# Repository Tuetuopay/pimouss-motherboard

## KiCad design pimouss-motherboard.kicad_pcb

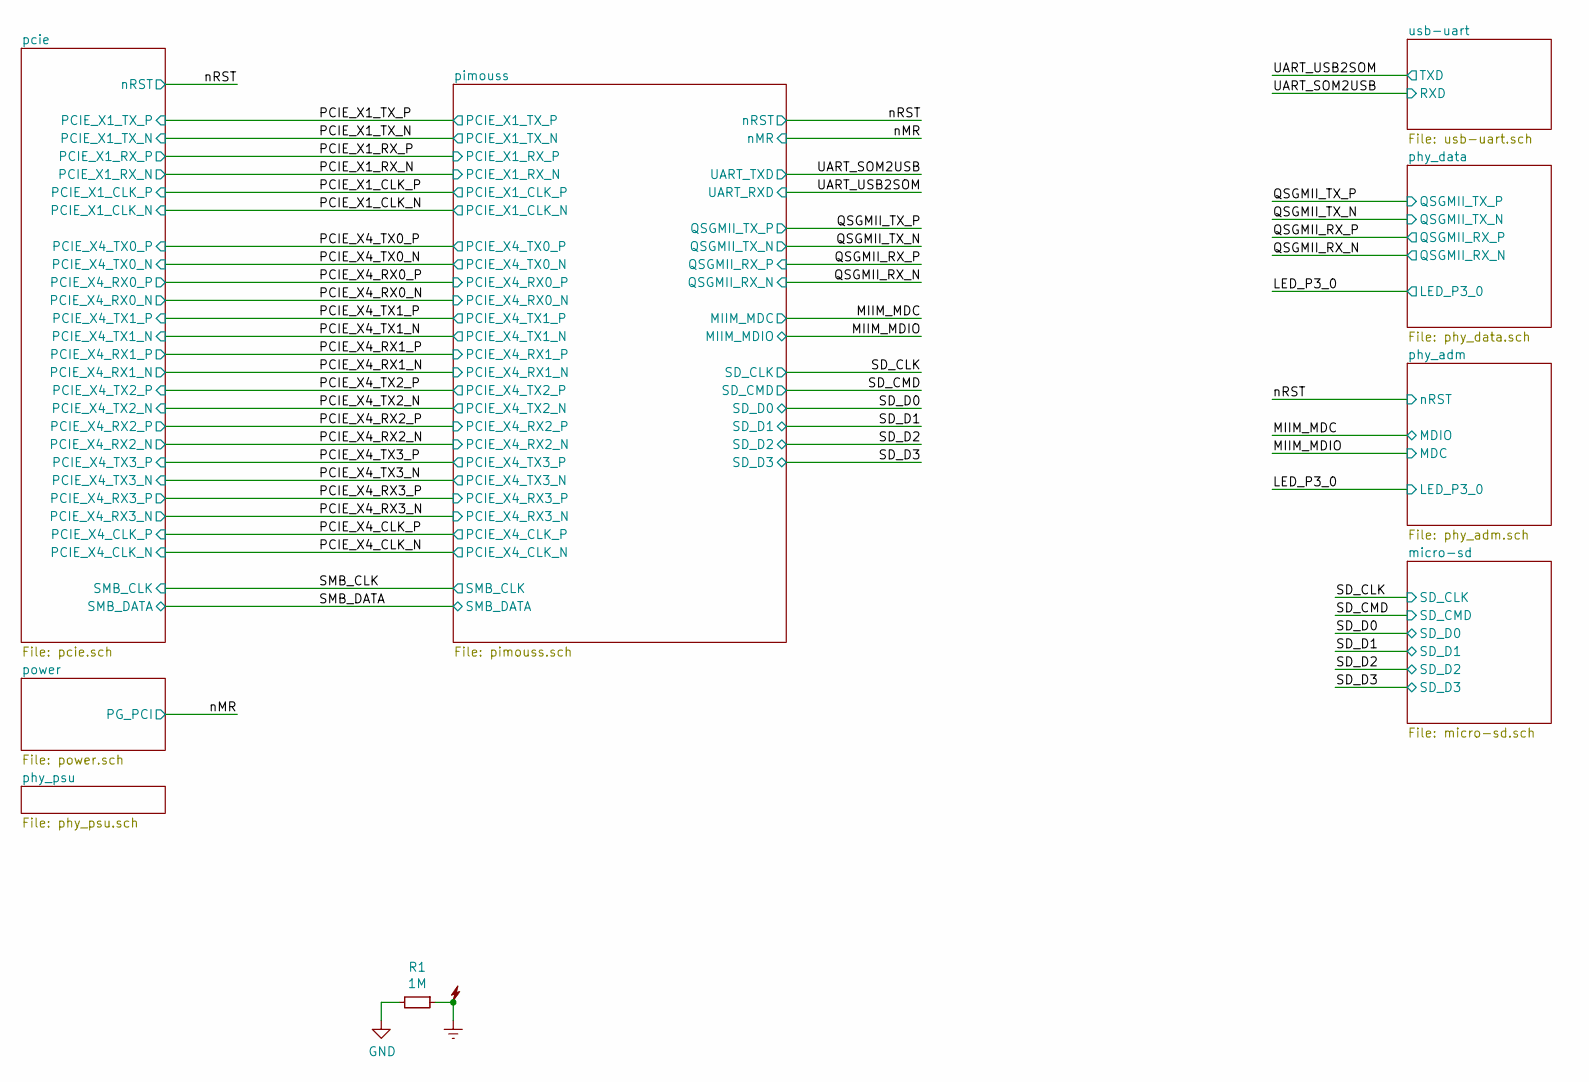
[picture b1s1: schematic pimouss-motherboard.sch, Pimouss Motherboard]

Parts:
R1: 1M; R_0603_1608Metric

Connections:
Earth: R1.1; also elsewhere on the board

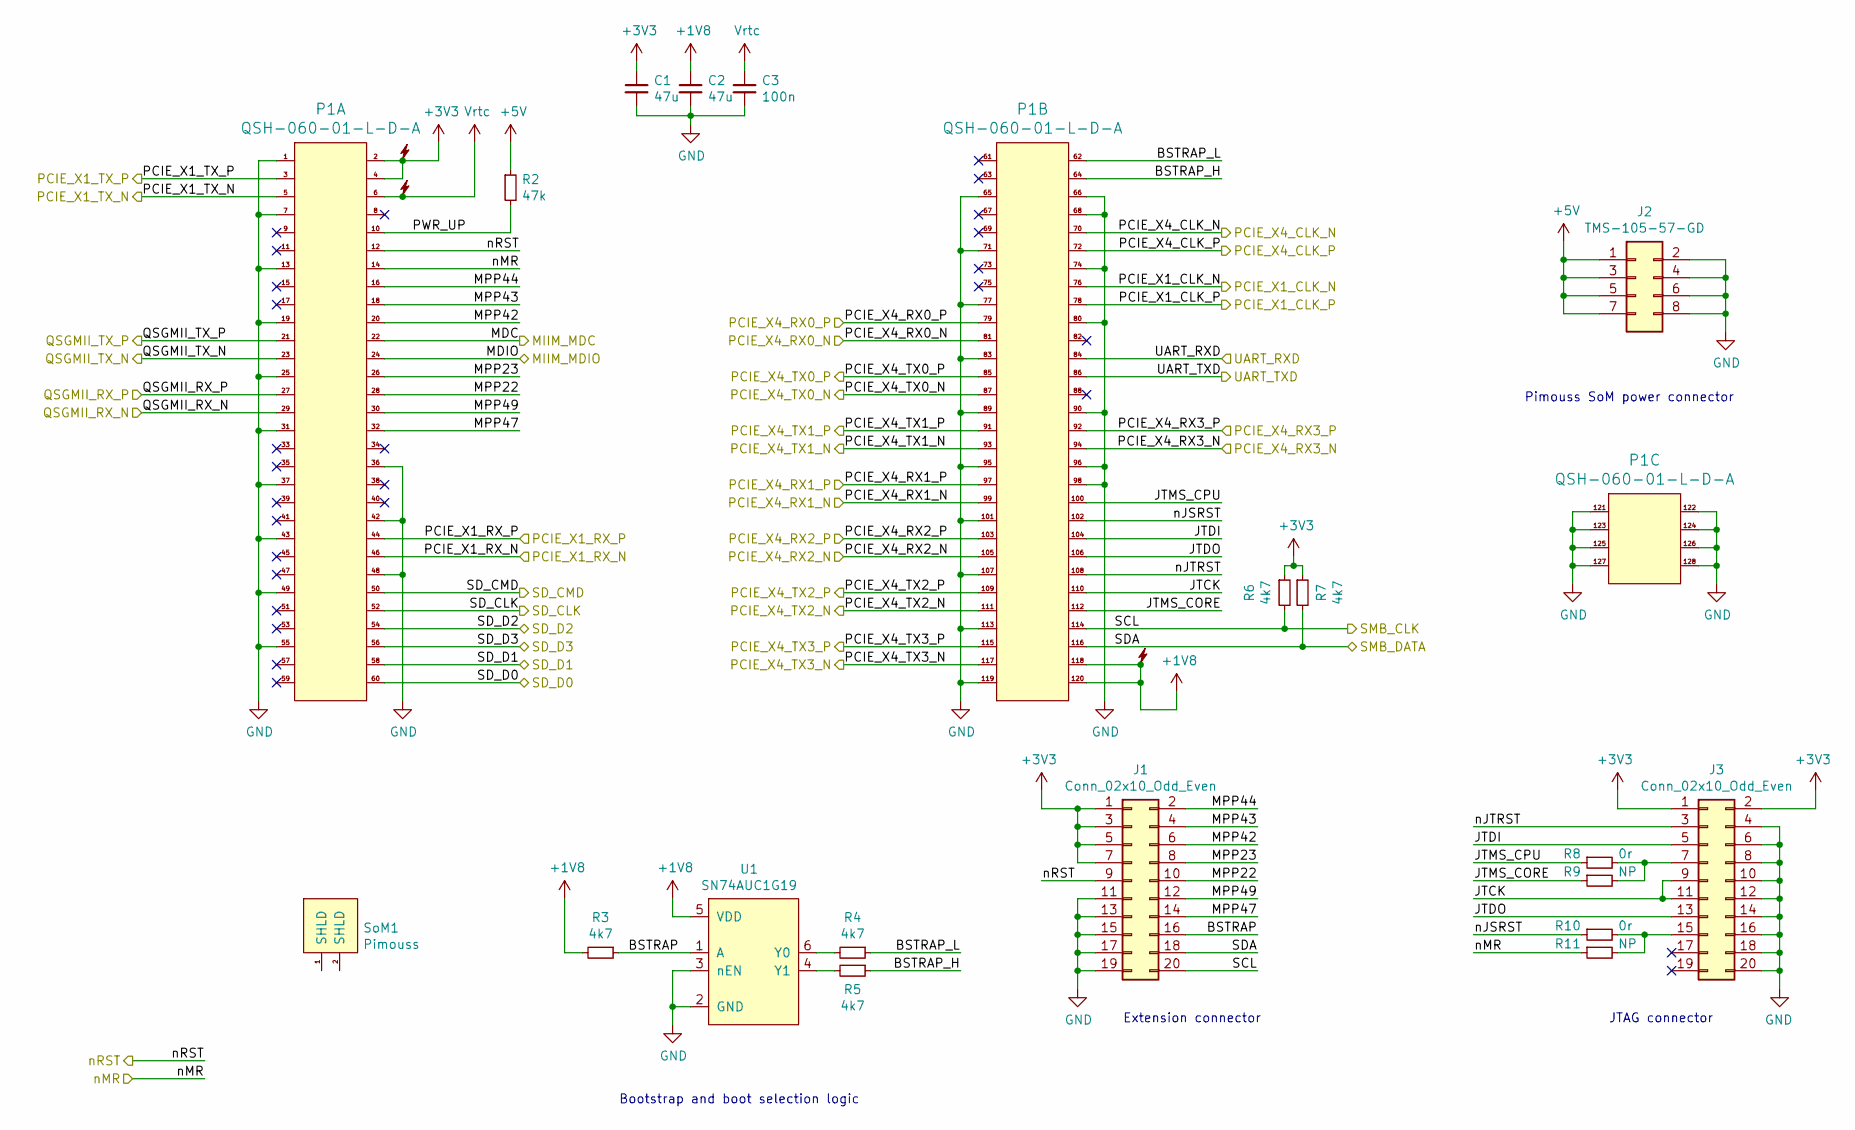
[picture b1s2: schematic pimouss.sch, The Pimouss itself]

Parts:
C1, C2: 47u; C_0805_2012Metric
C3: 100n; C_0603_1608Metric
J1, J3: Conn_02x10_Odd_Even; PinHeader_2x10_P2.54mm_Vertical
J2: TMS-105-57-GD; TMS-105-57-G-D
P1: QSH-060-01-L-D-A
R2: 47k; R_0603_1608Metric
R3, R4, R5, R6, R7: 4k7; R_0603_1608Metric
R8, R10: 0r; R_0603_1608Metric
R9, R11: NP; R_0603_1608Metric
SoM1: Pimouss
U1: SN74AUC1G19; SOT-23-6

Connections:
/MIIM_MDC: P1.22; also elsewhere on the board
/MIIM_MDIO: P1.24; also elsewhere on the board
/PCIE_X1_CLK_N: P1.76; also elsewhere on the board
/PCIE_X1_CLK_P: P1.78; also elsewhere on the board
/PCIE_X1_RX_N: P1.46; also elsewhere on the board
/PCIE_X1_RX_P: P1.44; also elsewhere on the board
/PCIE_X1_TX_N: P1.5; also elsewhere on the board
/PCIE_X1_TX_P: P1.3; also elsewhere on the board
/PCIE_X4_CLK_N: P1.70; also elsewhere on the board
/PCIE_X4_CLK_P: P1.72; also elsewhere on the board
/PCIE_X4_RX0_N: P1.81; also elsewhere on the board
/PCIE_X4_RX0_P: P1.79; also elsewhere on the board
/PCIE_X4_RX1_N: P1.99; also elsewhere on the board
/PCIE_X4_RX1_P: P1.97; also elsewhere on the board
/PCIE_X4_RX2_N: P1.105; also elsewhere on the board
/PCIE_X4_RX2_P: P1.103; also elsewhere on the board
/PCIE_X4_RX3_N: P1.94; also elsewhere on the board
/PCIE_X4_RX3_P: P1.92; also elsewhere on the board
/PCIE_X4_TX0_N: P1.87; also elsewhere on the board
/PCIE_X4_TX0_P: P1.85; also elsewhere on the board
/PCIE_X4_TX1_N: P1.93; also elsewhere on the board
/PCIE_X4_TX1_P: P1.91; also elsewhere on the board
/PCIE_X4_TX2_N: P1.111; also elsewhere on the board
/PCIE_X4_TX2_P: P1.109; also elsewhere on the board
/PCIE_X4_TX3_N: P1.117; also elsewhere on the board
/PCIE_X4_TX3_P: P1.115; also elsewhere on the board
/QSGMII_RX_N: P1.29; also elsewhere on the board
/QSGMII_RX_P: P1.27; also elsewhere on the board
/QSGMII_TX_N: P1.23; also elsewhere on the board
/QSGMII_TX_P: P1.21; also elsewhere on the board
/SD_CLK: P1.52; also elsewhere on the board
/SD_CMD: P1.50; also elsewhere on the board
/SD_D0: P1.60; also elsewhere on the board
/SD_D1: P1.58; also elsewhere on the board
/SD_D2: P1.54; also elsewhere on the board
/SD_D3: P1.56; also elsewhere on the board
/SMB_CLK: J1.20, P1.114, R6.2; also elsewhere on the board
/SMB_DATA: J1.18, P1.116, R7.2; also elsewhere on the board
/UART_SOM2USB: P1.86; also elsewhere on the board
/UART_USB2SOM: P1.84; also elsewhere on the board
/nMR: P1.14, R11.1; also elsewhere on the board
/nRST: J1.9, P1.12; also elsewhere on the board
/pimouss/BSTRAP: J1.16, R3.1, U1.1 (A)
/pimouss/BSTRAP_H: P1.64, R5.1
/pimouss/BSTRAP_L: P1.62, R4.1
/pimouss/JTCK: J3.9, J3.11, P1.110
/pimouss/JTDI: J3.5, P1.104
/pimouss/JTDO: J3.13, P1.106
/pimouss/JTMS_CORE: P1.112, R9.1
/pimouss/JTMS_CPU: P1.100, R8.1
/pimouss/MPP22: J1.10, P1.28
/pimouss/MPP23: J1.8, P1.26
/pimouss/MPP42: J1.6, P1.20
/pimouss/MPP43: J1.4, P1.18
/pimouss/MPP44: J1.2, P1.16
/pimouss/MPP47: J1.14, P1.32
/pimouss/MPP49: J1.12, P1.30
/pimouss/PWR_UP: P1.10, R2.2
/pimouss/nJSRST: P1.102, R10.1
/pimouss/nJTRST: J3.3, P1.108
unnamed: J3.7, R8.2, R9.2
unnamed: J3.15, R10.2, R11.2
unnamed: R4.2, U1.6 (Y0)
unnamed: R5.2, U1.4 (Y1)

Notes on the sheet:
Pimouss SoM power connector
Bootstrap and boot selection logic
JTAG connector
Extension connector

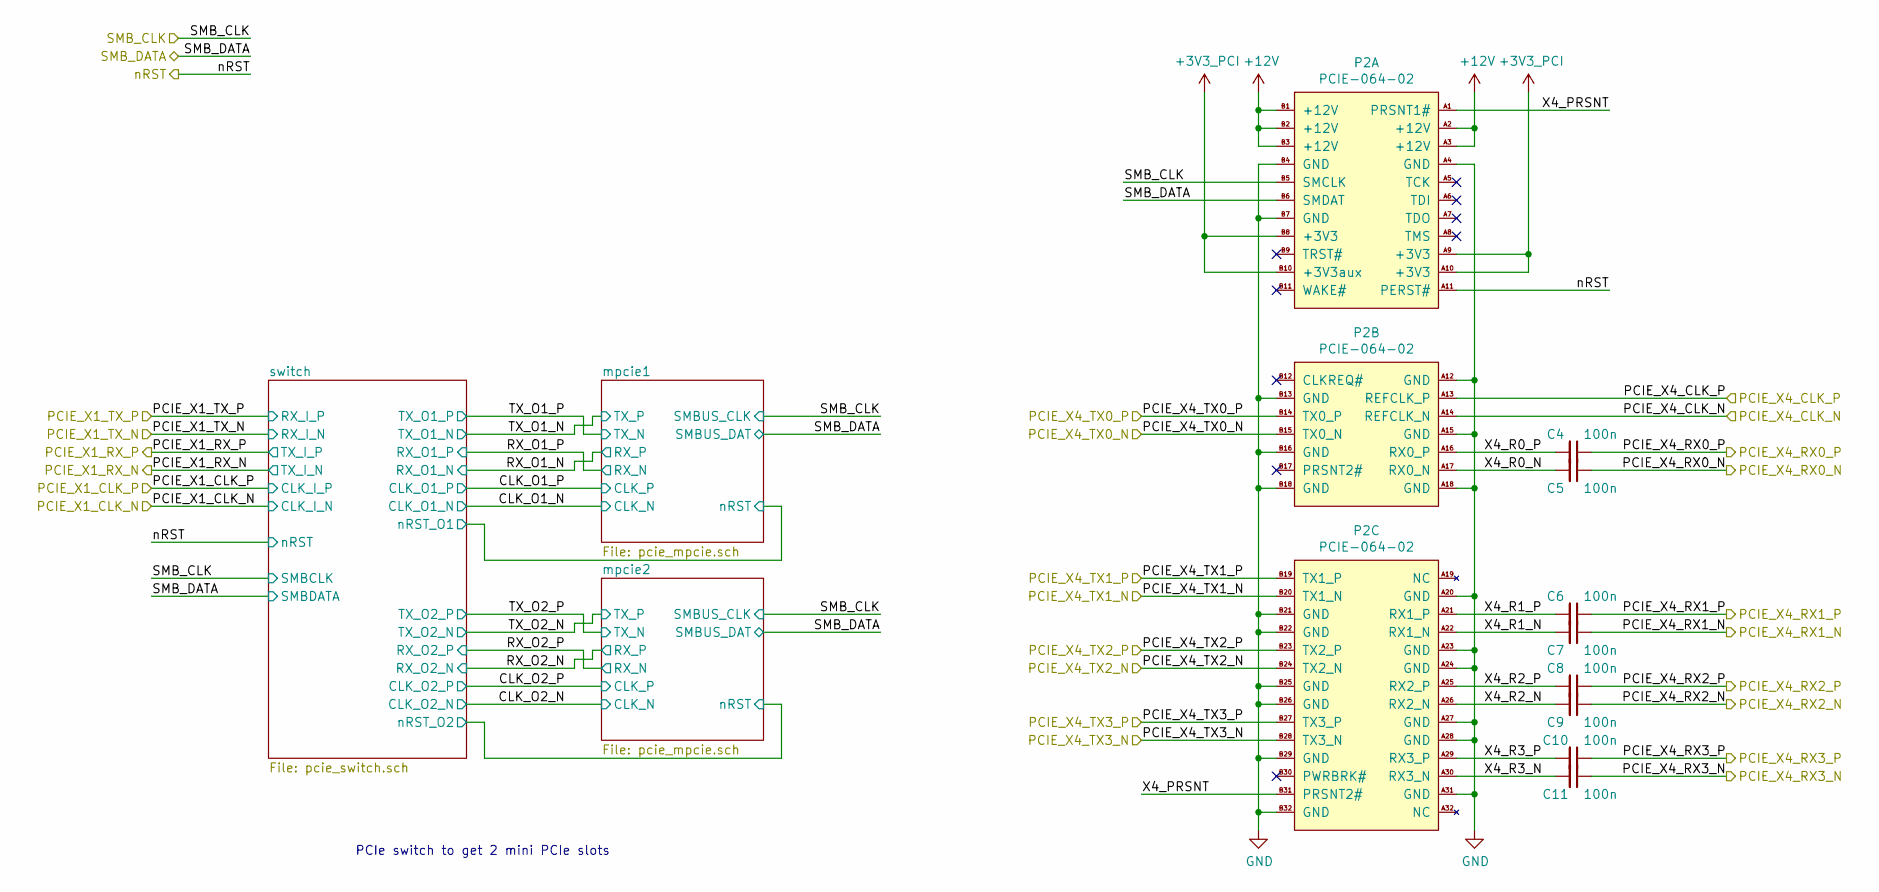
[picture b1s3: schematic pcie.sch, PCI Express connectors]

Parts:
C4, C5, C6, C7, C8, C9, C10, C11: 100n; C_0402_1005Metric
P2: PCIE-064-02; SAMTEC_PCIE-064-02-F-D-TH

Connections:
/PCIE_X4_CLK_N: P2.A14 (REFCLK_N); also elsewhere on the board
/PCIE_X4_CLK_P: P2.A13 (REFCLK_P); also elsewhere on the board
/PCIE_X4_RX0_N: C5.1; also elsewhere on the board
/PCIE_X4_RX0_P: C4.1; also elsewhere on the board
/PCIE_X4_RX1_N: C7.1; also elsewhere on the board
/PCIE_X4_RX1_P: C6.1; also elsewhere on the board
/PCIE_X4_RX2_N: C9.1; also elsewhere on the board
/PCIE_X4_RX2_P: C8.1; also elsewhere on the board
/PCIE_X4_RX3_N: C11.1; also elsewhere on the board
/PCIE_X4_RX3_P: C10.1; also elsewhere on the board
/PCIE_X4_TX0_N: P2.B15 (TX0_N); also elsewhere on the board
/PCIE_X4_TX0_P: P2.B14 (TX0_P); also elsewhere on the board
/PCIE_X4_TX1_N: P2.B20 (TX1_N); also elsewhere on the board
/PCIE_X4_TX1_P: P2.B19 (TX1_P); also elsewhere on the board
/PCIE_X4_TX2_N: P2.B24 (TX2_N); also elsewhere on the board
/PCIE_X4_TX2_P: P2.B23 (TX2_P); also elsewhere on the board
/PCIE_X4_TX3_N: P2.B28 (TX3_N); also elsewhere on the board
/PCIE_X4_TX3_P: P2.B27 (TX3_P); also elsewhere on the board
/SMB_CLK: P2.B5 (SMCLK); also elsewhere on the board
/SMB_DATA: P2.B6 (SMDAT); also elsewhere on the board
/nRST: P2.A11 (PERST#); also elsewhere on the board
/pcie/X4_PRSNT: P2.A1 (PRSNT1#), P2.B31 (PRSNT2#)
/pcie/X4_R0_N: C5.2, P2.A17 (RX0_N)
/pcie/X4_R0_P: C4.2, P2.A16 (RX0_P)
/pcie/X4_R1_N: C7.2, P2.A22 (RX1_N)
/pcie/X4_R1_P: C6.2, P2.A21 (RX1_P)
/pcie/X4_R2_N: C9.2, P2.A26 (RX2_N)
/pcie/X4_R2_P: C8.2, P2.A25 (RX2_P)
/pcie/X4_R3_N: C11.2, P2.A30 (RX3_N)
/pcie/X4_R3_P: C10.2, P2.A29 (RX3_P)

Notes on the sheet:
PCIe switch to get 2 mini PCIe slots

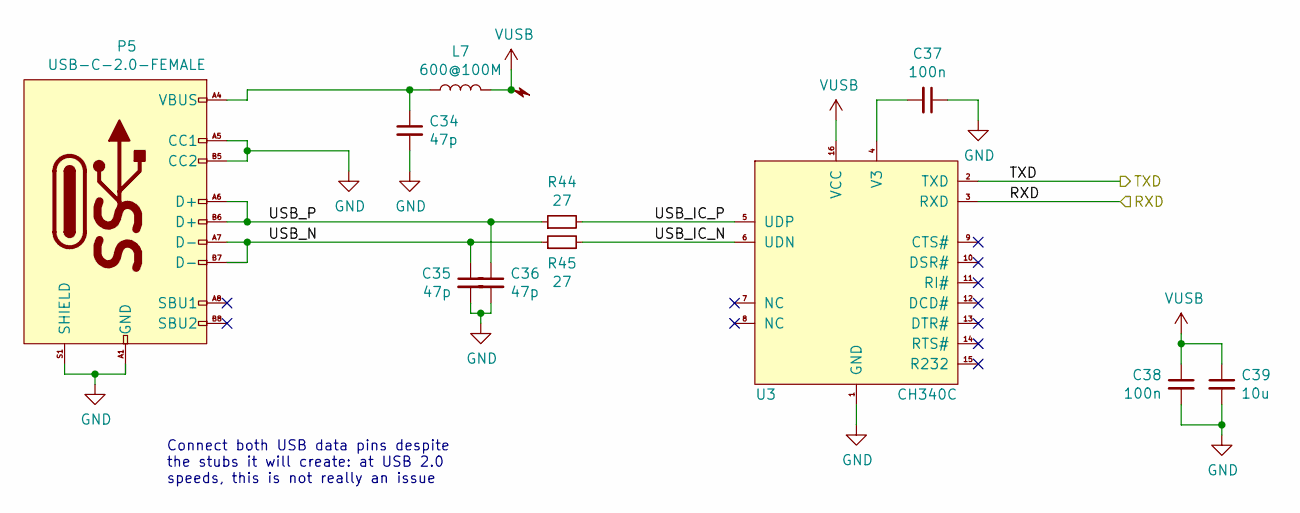
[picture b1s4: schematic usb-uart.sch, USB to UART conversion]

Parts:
C34, C35, C36: 47p; C_0603_1608Metric
C37, C38: 100n; C_0603_1608Metric
C39: 10u; C_0603_1608Metric
L7: 600@100M; L_0603_1608Metric
P5: USB-C-2.0-FEMALE; USB-C-FEMALE
R44, R45: 27; R_0603_1608Metric
U3: CH340C; SSOP-20_5.3x7.2mm_P0.65mm

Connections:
/UART_SOM2USB: U3.3 (RXD); also elsewhere on the board
/UART_USB2SOM: U3.2 (TXD); also elsewhere on the board
/usb-uart/USB_IC_N: R45.2, U3.6 (UDN)
/usb-uart/USB_IC_P: R44.2, U3.5 (UDP)
/usb-uart/USB_N: C35.1, P5.A7 (D-), P5.B7 (D-), R45.1
/usb-uart/USB_P: C36.1, P5.A6 (D+), P5.B6 (D+), R44.1
unnamed: C34.1, L7.1, P5.A4 (VBUS), P5.A9 (VBUS), P5.B4 (VBUS), P5.B9 (VBUS)
unnamed: C37.2, U3.4 (V3)
VUSB: C38.1, C39.1, L7.2, U3.16 (VCC)

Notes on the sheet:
Connect both USB data pins despite the stubs it will create: at USB 2.0 speeds, this is not really an issue

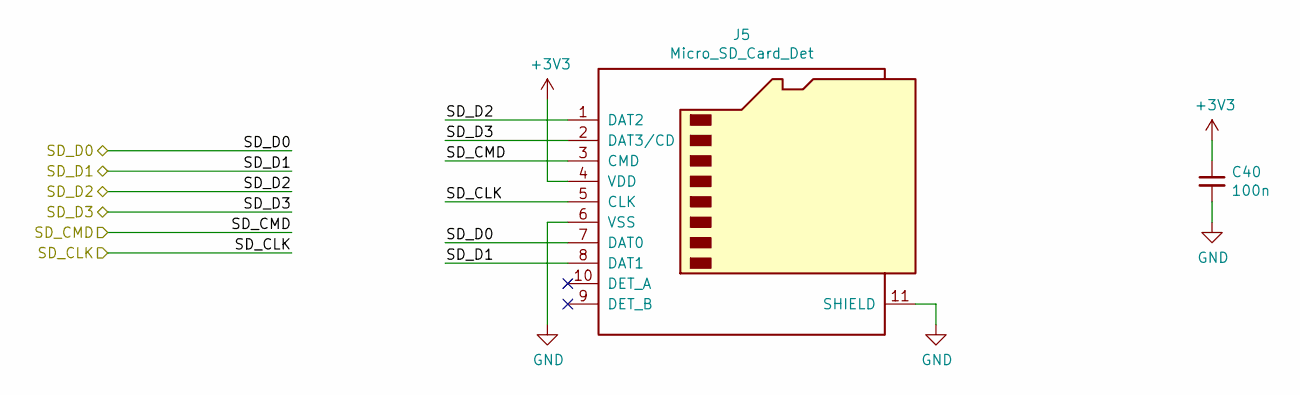
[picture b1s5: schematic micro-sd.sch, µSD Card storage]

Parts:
C40: 100n; C_0603_1608Metric
J5: Micro_SD_Card_Det; microSD_HC_Hirose_DM3D-SF

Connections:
/SD_CLK: J5.5 (CLK); also elsewhere on the board
/SD_CMD: J5.3 (CMD); also elsewhere on the board
/SD_D0: J5.7 (DAT0); also elsewhere on the board
/SD_D1: J5.8 (DAT1); also elsewhere on the board
/SD_D2: J5.1 (DAT2); also elsewhere on the board
/SD_D3: J5.2 (DAT3/CD); also elsewhere on the board

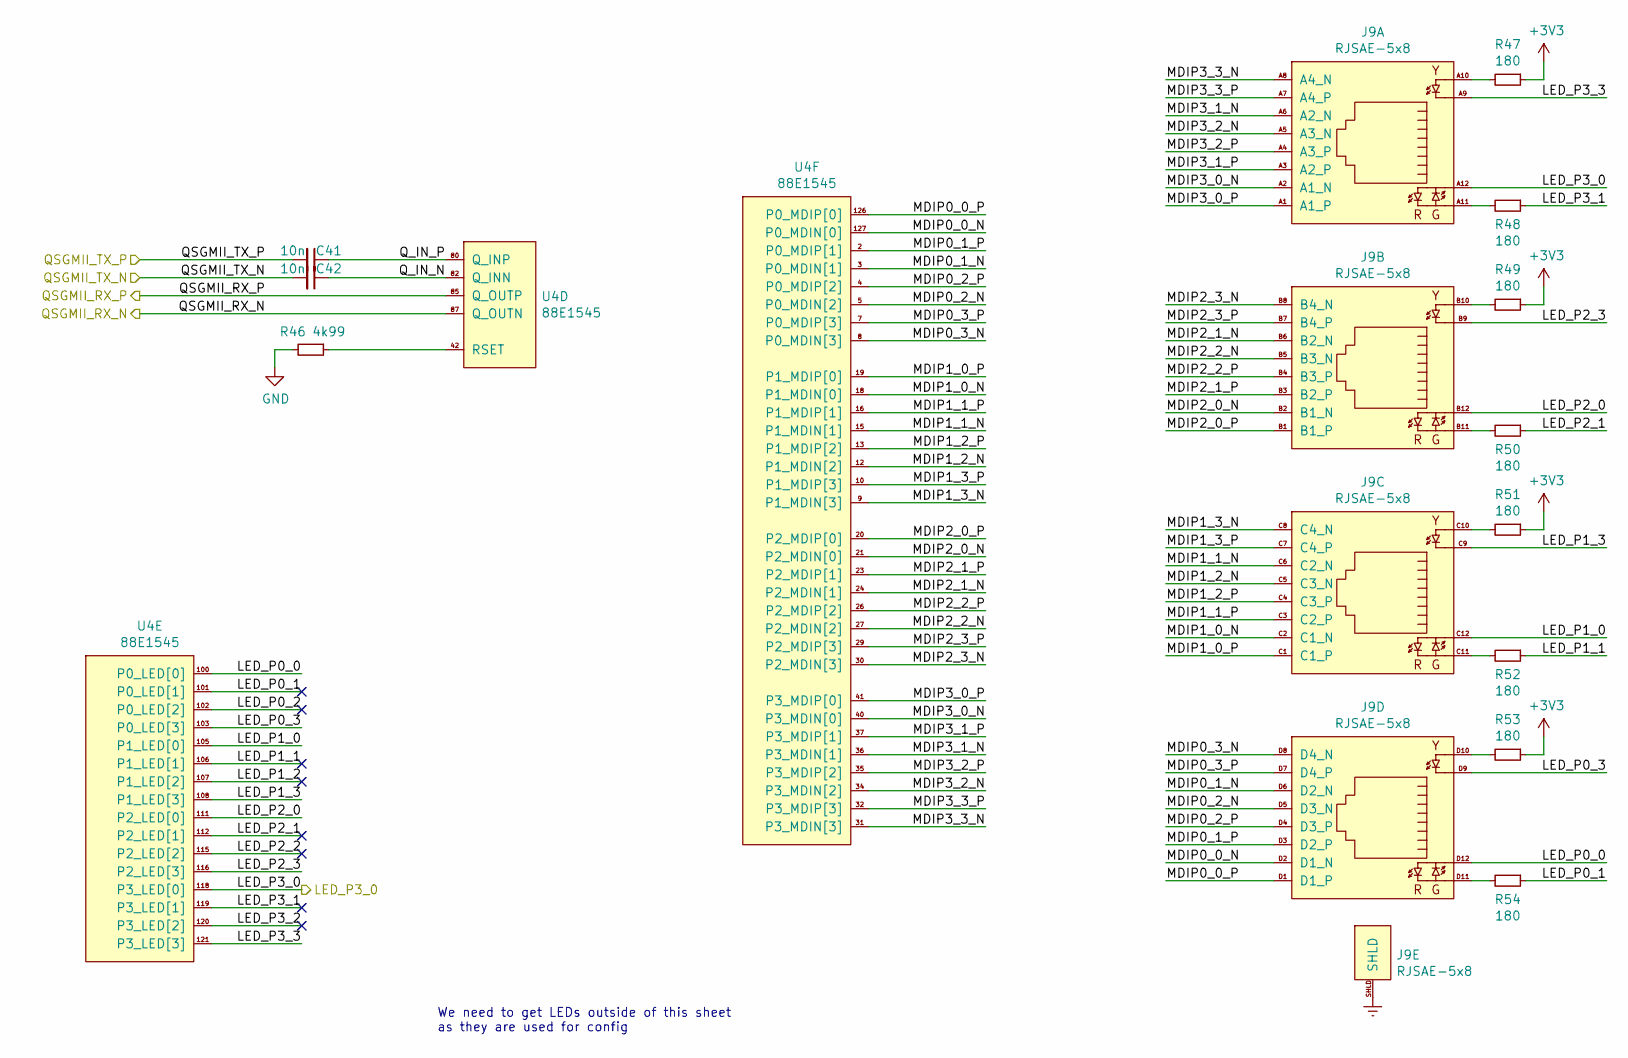
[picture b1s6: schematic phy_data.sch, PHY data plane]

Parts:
C41, C42: 10n; C_0402_1005Metric
J9: RJSAE-5x8
R46: 4k99; R_0603_1608Metric
R47, R48, R49, R50, R51, R52, R53, R54: 180; R_0603_1608Metric
U4: 88E1545; LQFP-128-1EP_14x20mm_P0.5mm_EP3.93x6.42mm

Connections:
/LED_P3_0: J9.A12, U4.118 (P3_LED[0]); also elsewhere on the board
/QSGMII_RX_N: U4.87 (Q_OUTN); also elsewhere on the board
/QSGMII_RX_P: U4.85 (Q_OUTP); also elsewhere on the board
/QSGMII_TX_N: C42.2; also elsewhere on the board
/QSGMII_TX_P: C41.2; also elsewhere on the board
/phy_data/LED_P0_0: J9.D12, U4.100 (P0_LED[0])
/phy_data/LED_P0_1: R54.1, U4.101 (P0_LED[1])
/phy_data/LED_P0_2: U4.102 (P0_LED[2])
/phy_data/LED_P0_3: J9.D9, U4.103 (P0_LED[3])
/phy_data/LED_P1_0: J9.C12, U4.105 (P1_LED[0])
/phy_data/LED_P1_1: R52.1, U4.106 (P1_LED[1])
/phy_data/LED_P1_2: U4.107 (P1_LED[2])
/phy_data/LED_P1_3: J9.C9, U4.108 (P1_LED[3])
/phy_data/LED_P2_0: J9.B12, U4.111 (P2_LED[0])
/phy_data/LED_P2_1: R50.1, U4.112 (P2_LED[1])
/phy_data/LED_P2_2: U4.115 (P2_LED[2])
/phy_data/LED_P2_3: J9.B9, U4.116 (P2_LED[3])
/phy_data/LED_P3_1: R48.1, U4.119 (P3_LED[1])
/phy_data/LED_P3_2: U4.120 (P3_LED[2])
/phy_data/LED_P3_3: J9.A9, U4.121 (P3_LED[3])
/phy_data/MDIP0_0_N: J9.D2 (D1_N), U4.127 (P0_MDIN[0])
/phy_data/MDIP0_0_P: J9.D1 (D1_P), U4.126 (P0_MDIP[0])
/phy_data/MDIP0_1_N: J9.D6 (D2_N), U4.3 (P0_MDIN[1])
/phy_data/MDIP0_1_P: J9.D3 (D2_P), U4.2 (P0_MDIP[1])
/phy_data/MDIP0_2_N: J9.D5 (D3_N), U4.5 (P0_MDIN[2])
/phy_data/MDIP0_2_P: J9.D4 (D3_P), U4.4 (P0_MDIP[2])
/phy_data/MDIP0_3_N: J9.D8 (D4_N), U4.8 (P0_MDIN[3])
/phy_data/MDIP0_3_P: J9.D7 (D4_P), U4.7 (P0_MDIP[3])
/phy_data/MDIP1_0_N: J9.C2 (C1_N), U4.18 (P1_MDIN[0])
/phy_data/MDIP1_0_P: J9.C1 (C1_P), U4.19 (P1_MDIP[0])
/phy_data/MDIP1_1_N: J9.C6 (C2_N), U4.15 (P1_MDIN[1])
/phy_data/MDIP1_1_P: J9.C3 (C2_P), U4.16 (P1_MDIP[1])
/phy_data/MDIP1_2_N: J9.C5 (C3_N), U4.12 (P1_MDIN[2])
/phy_data/MDIP1_2_P: J9.C4 (C3_P), U4.13 (P1_MDIP[2])
/phy_data/MDIP1_3_N: J9.C8 (C4_N), U4.9 (P1_MDIN[3])
/phy_data/MDIP1_3_P: J9.C7 (C4_P), U4.10 (P1_MDIP[3])
/phy_data/MDIP2_0_N: J9.B2 (B1_N), U4.21 (P2_MDIN[0])
/phy_data/MDIP2_0_P: J9.B1 (B1_P), U4.20 (P2_MDIP[0])
/phy_data/MDIP2_1_N: J9.B6 (B2_N), U4.24 (P2_MDIN[1])
/phy_data/MDIP2_1_P: J9.B3 (B2_P), U4.23 (P2_MDIP[1])
/phy_data/MDIP2_2_N: J9.B5 (B3_N), U4.27 (P2_MDIN[2])
/phy_data/MDIP2_2_P: J9.B4 (B3_P), U4.26 (P2_MDIP[2])
/phy_data/MDIP2_3_N: J9.B8 (B4_N), U4.30 (P2_MDIN[3])
/phy_data/MDIP2_3_P: J9.B7 (B4_P), U4.29 (P2_MDIP[3])
/phy_data/MDIP3_0_N: J9.A2 (A1_N), U4.40 (P3_MDIN[0])
/phy_data/MDIP3_0_P: J9.A1 (A1_P), U4.41 (P3_MDIP[0])
/phy_data/MDIP3_1_N: J9.A6 (A2_N), U4.36 (P3_MDIN[1])
/phy_data/MDIP3_1_P: J9.A3 (A2_P), U4.37 (P3_MDIP[1])
/phy_data/MDIP3_2_N: J9.A5 (A3_N), U4.34 (P3_MDIN[2])
/phy_data/MDIP3_2_P: J9.A4 (A3_P), U4.35 (P3_MDIP[2])
/phy_data/MDIP3_3_N: J9.A8 (A4_N), U4.31 (P3_MDIN[3])
/phy_data/MDIP3_3_P: J9.A7 (A4_P), U4.32 (P3_MDIP[3])
/phy_data/Q_IN_N: C42.1, U4.82 (Q_INN)
/phy_data/Q_IN_P: C41.1, U4.80 (Q_INP)
Earth: J9.SHLD; also elsewhere on the board
unnamed: J9.A10, R47.2
unnamed: J9.A11, R48.2
unnamed: J9.B10, R49.2
unnamed: J9.B11, R50.2
unnamed: J9.C10, R51.2
unnamed: J9.C11, R52.2
unnamed: J9.D10, R53.2
unnamed: J9.D11, R54.2
unnamed: R46.1, U4.42 (RSET)

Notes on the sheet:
We need to get LEDs outside of this sheet as they are used for config

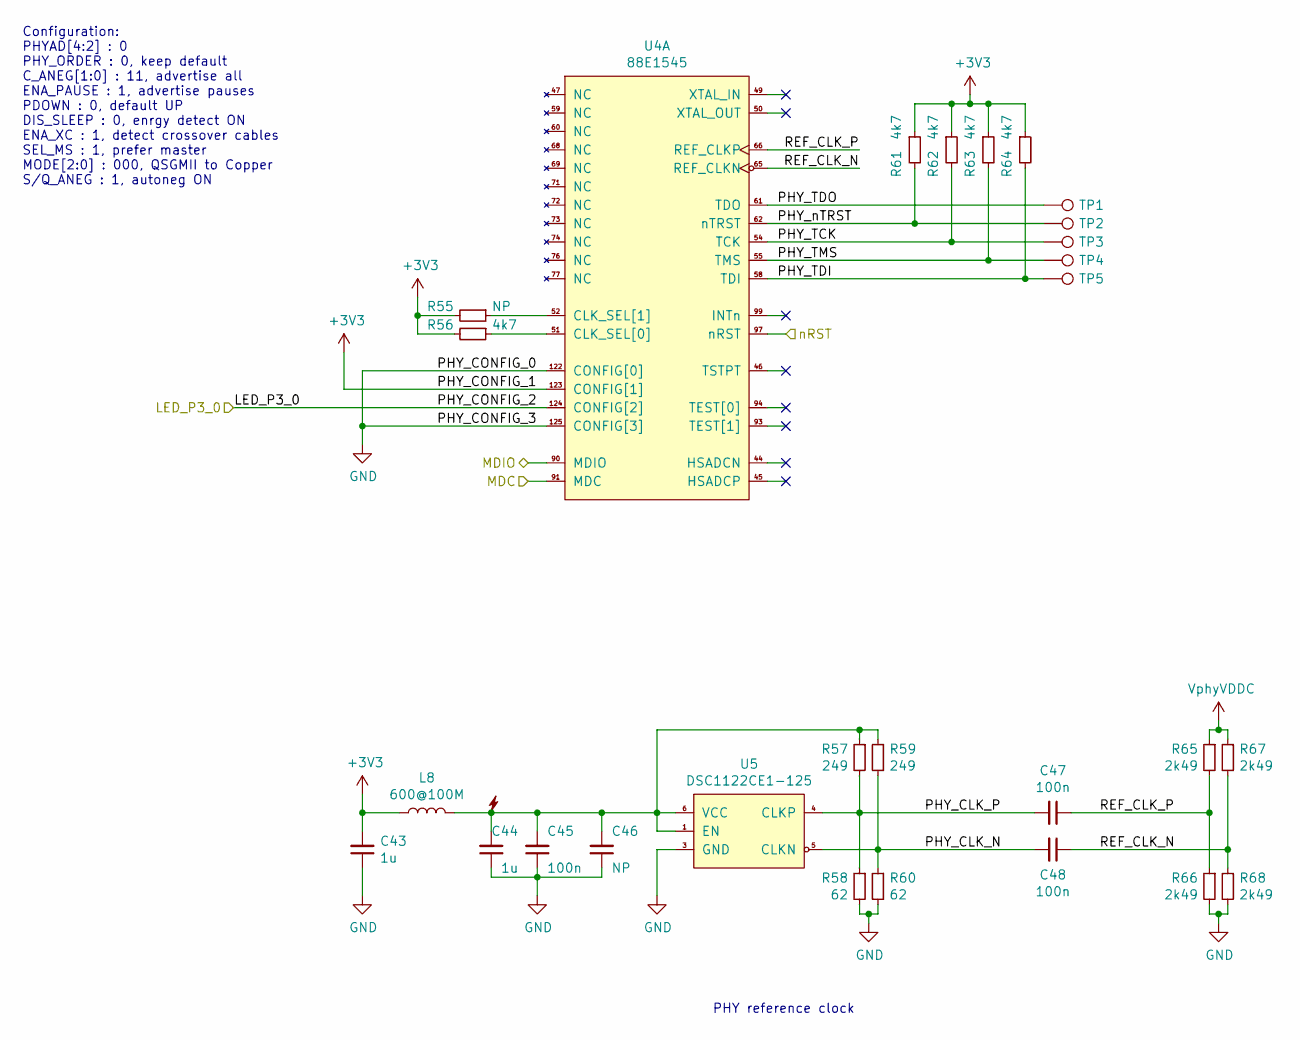
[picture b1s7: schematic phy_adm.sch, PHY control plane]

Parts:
C43, C44: 1u; C_0603_1608Metric
C45: 100n; C_0603_1608Metric
C46: NP; C_0603_1608Metric
C47, C48: 100n; C_0402_1005Metric
L8: 600@100M; L_0603_1608Metric
R55: NP; R_0603_1608Metric
R56, R61, R62, R63, R64: 4k7; R_0603_1608Metric
R57, R59: 249; R_0402_1005Metric
R58, R60: 62; R_0402_1005Metric
R65, R66, R67, R68: 2k49; R_0402_1005Metric
TP1, TP2, TP3, TP4, TP5: TestPoint; TestPoint_Pad_D1.0mm
U4: 88E1545; LQFP-128-1EP_14x20mm_P0.5mm_EP3.93x6.42mm
U5: DSC1122CE1-125; DFN-6_2.5x2mm_P0.825mm

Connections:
/LED_P3_0: U4.124 (CONFIG[2]); also elsewhere on the board
/MIIM_MDC: U4.90 (MDIO); also elsewhere on the board
/MIIM_MDIO: U4.91 (MDC); also elsewhere on the board
/nRST: U4.97 (nRST); also elsewhere on the board
/phy_adm/PHY_CLK_N: C48.2, R59.2, R60.1, U5.5 (CLKN)
/phy_adm/PHY_CLK_P: C47.2, R57.2, R58.1, U5.4 (CLKP)
/phy_adm/PHY_TCK: R62.2, TP3.1, U4.54 (TCK)
/phy_adm/PHY_TDI: R64.2, TP5.1, U4.58 (TDI)
/phy_adm/PHY_TDO: TP1.1, U4.61 (TDO)
/phy_adm/PHY_TMS: R63.2, TP4.1, U4.55 (TMS)
/phy_adm/PHY_nTRST: R61.2, TP2.1, U4.62 (nTRST)
/phy_adm/REF_CLK_N: C48.1, R67.2, R68.1, U4.65 (REF_CLKN)
/phy_adm/REF_CLK_P: C47.1, R65.2, R66.1, U4.66 (REF_CLKP)
unnamed: C44.2, C45.2, C46.2, L8.2, R57.1, R59.1, U5.1 (EN), U5.6 (VCC)
unnamed: R55.1, U4.52 (CLK_SEL[1])
unnamed: R56.1, U4.51 (CLK_SEL[0])

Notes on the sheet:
Configuration: PHYAD[4:2] : 0 PHY_ORDER : 0, keep default C_ANEG[1:0] : 11, advertise all ENA_PAUSE : 1, advertise pauses PDOWN : 0, default UP DIS_SLEEP : 0, enrgy detect ON ENA_XC : 1, detect crossover cables SEL_MS : 1, prefer master MODE[2:0] : 000, QSGMII to Copper S/Q_ANEG : 1, autoneg ON
PHY reference clock

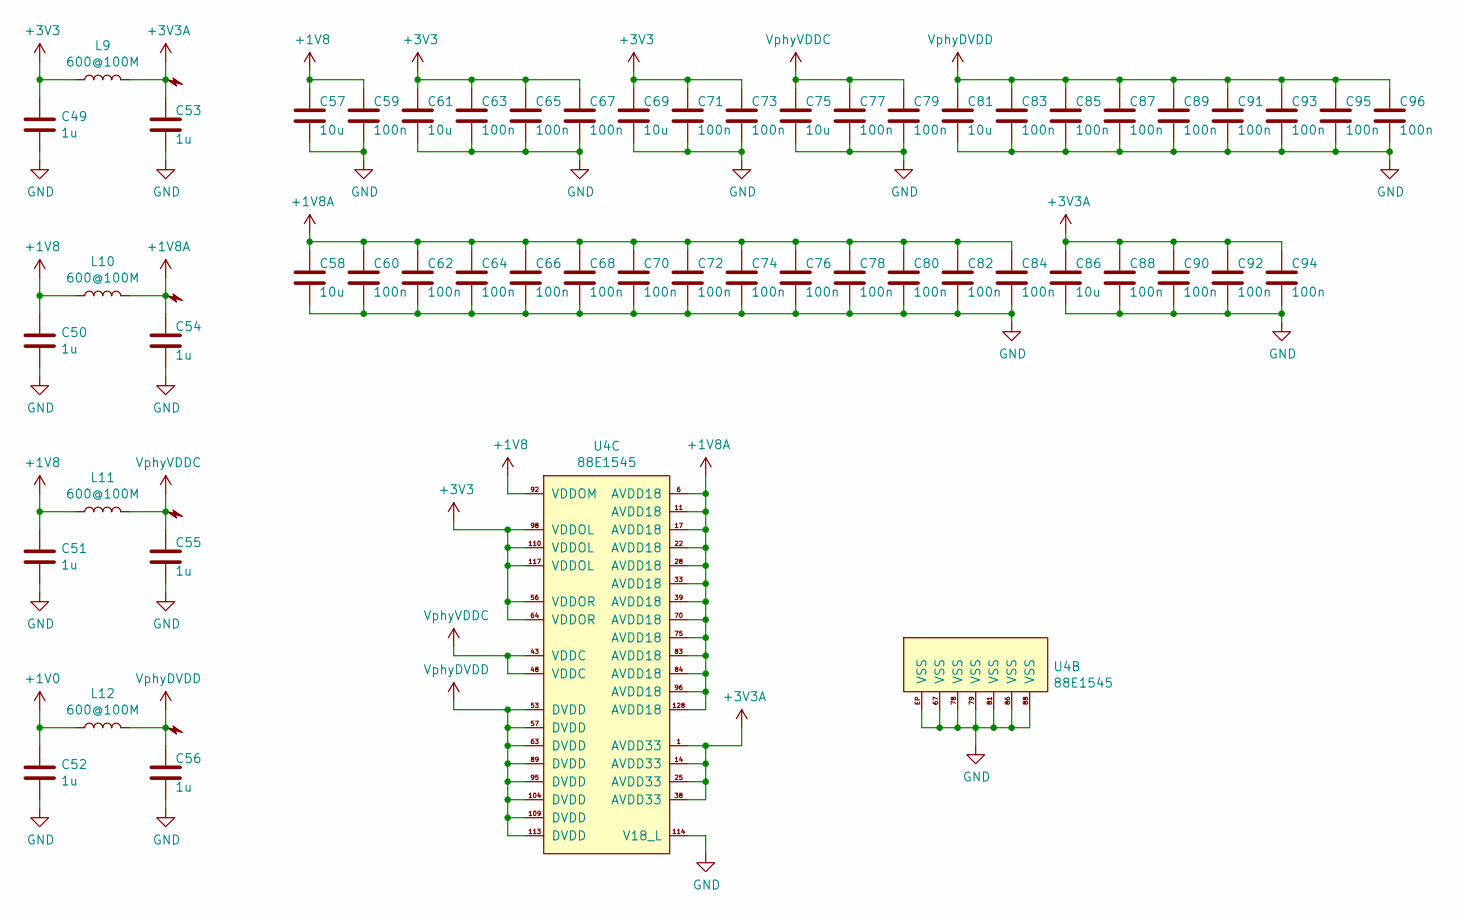
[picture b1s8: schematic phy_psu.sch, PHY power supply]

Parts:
C49, C50, C51, C52, C53, C54, C55, C56: 1u; C_0603_1608Metric
C57, C58, C61, C69, C75, C81, C86: 10u; C_0603_1608Metric
C59, C60, C62, C63, C64, C65, C66, C67, C68, C70, C71, C72, C73, C74, C76, C77, C78, C79, C80, C82, C83, C84, C85, C87, C88, C89, C90, C91, C92, C93, C94, C95, C96: 100n; C_0603_1608Metric
L9, L10, L11, L12: 600@100M; L_0603_1608Metric
U4: 88E1545; LQFP-128-1EP_14x20mm_P0.5mm_EP3.93x6.42mm

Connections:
+1V0: C52.1, L12.1; also elsewhere on the board

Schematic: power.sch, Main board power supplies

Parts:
C97, C98, C99, C100, C101, C102, C151, C152: 22u; C_0805_2012Metric
C103: 470u; CP_Elec_10x10
C104, C105: 12p; C_0603_1608Metric
C106, C107: 1u; C_0603_1608Metric
C108: 10n; C_0603_1608Metric
C109: 4u7; C_0603_1608Metric
C110, C111, C113, C114, C116, C117, C118: 100n; C_0603_1608Metric
C112: 10u; C_0603_1608Metric
C115: 2u2; C_0603_1608Metric
J10: Barrel_Jack_Switch; BarrelJack_Horizontal
L13, L14: 1u5; L_Vishay_IHHP-0806
L15, L16: 2u2; L_Vishay_IHHP-0806
R69, R77, R79, R80: 10k; R_0603_1608Metric
R70: 312k5; R_0603_1608Metric
R71, R73, R78: 100k; R_0603_1608Metric
R72: 87k5; R_0603_1608Metric
R74: 1k13; R_0603_1608Metric
R75: 4k53; R_0603_1608Metric
R76, R81: 73k2; R_0603_1608Metric
U6: ISL8033A; QFN-24-1EP_4x4mm_P0.5mm_EP2.6x2.6mm
U7: TPS74401_VQFN; Texas_S-PVQFN-N20_EP3.15x3.15mm_ThermalVias
U8: LTC3633; QFN-28-1EP_4x5mm_P0.5mm_EP2.65x3.65mm_ThermalVias

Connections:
+1V0: C112.1, R74.1, U7.1 (OUT), U7.18 (OUT), U7.19 (OUT), U7.20 (OUT); also elsewhere on the board
/nMR: R69.1, U6.5 (PG2), U6.11 (PG1); also elsewhere on the board
/power/INTVCC: C115.2, U8.2 (PHMODE), U8.4 (MODE/SYNC), U8.11 (ITH2), U8.18 (V2P5), U8.19 (INTVCC), U8.26 (ITH1)
/power/PG_5V: R79.1, U6.4 (EN2), U6.13 (EN1), U8.1 (PGOOD1), U8.8 (PGOOD2)
unnamed: C100.2, C102.2, U6.22 (PGND2), U6.23 (PGND2)
unnamed: C99.2, C101.2, U6.20 (PGND1), U6.21 (PGND1)
unnamed: C104.2, R70.2, R71.1, U6.6 (FB2)
unnamed: C105.2, R72.2, R73.1, U6.9 (FB1)
unnamed: C108.1, U7.15 (SS)
unnamed: C114.1, U8.17 (BOOST2)
unnamed: C114.2, L15.2, U8.13 (SW2), U8.14 (SW2)
unnamed: C116.1, U8.20 (BOOST1)
unnamed: C116.2, L16.2, U8.23 (SW1), U8.24 (SW1)
unnamed: L13.1, U6.18 (LX1), U6.19 (LX1)
unnamed: L14.1, U6.1 (LX2), U6.24 (LX2)
unnamed: R74.2, R75.1, U7.16 (FB)
unnamed: R76.1, R77.2, U8.9 (VFB2)
unnamed: R78.1, U8.5 (RT)
unnamed: R80.2, R81.1, U8.28 (VFB1)

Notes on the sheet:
On LTC3633, PG pins are open-drains and pull down when not good. PG_5V will be low if any channel is bad.
On ISL8033, PG pins are open-drains and pull down when not good. PG_PCI will be low if any channel is bad.

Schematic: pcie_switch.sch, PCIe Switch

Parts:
C12, C13, C15, C16, C20, C23: 1u; C_0603_1608Metric
C18, C19, C26, C27, C28, C29: 100n; C_0402_1005Metric
C119, C120, C132, C138, C139, C145: 10u; C_0603_1608Metric
C121, C122, C123, C124, C125, C126, C127, C128, C129, C130, C131, C133, C134, C135, C136, C137, C140, C141, C142, C143, C144, C146, C147, C148, C149, C150: 100n; C_0603_1608Metric
J4: Conn_01x03_Male; PinHeader_1x03_P2.54mm_Vertical
L1, L2, L4: 600@100M; L_0603_1608Metric
R12, R13, R18, R19, R20, R21: 33; R_0402_1005Metric
R14, R15, R16, R17, R22, R23, R24, R25: 49r9; R_0402_1005Metric
R26: 1k43; R_0603_1608Metric
R27: 475; R_0603_1608Metric
R28, R32, R33: 5k1; R_0603_1608Metric
R29, R30, R31: 10k; R_0603_1608Metric
R34, R35, R36, R37: 330; R_0603_1608Metric
U2: PI7C9X2G404SL; LQFP-128_1EP_14x14mm_P0.4mm_EP6x6mm

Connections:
+1V0: C12.1, C13.1, L1.1, L2.1; also elsewhere on the board
/PCIE_X1_CLK_N: R14.1, U2.73 (REFCLKI_N); also elsewhere on the board
/PCIE_X1_CLK_P: R16.1, U2.74 (REFCLKI_P); also elsewhere on the board
/PCIE_X1_RX_N: C19.2; also elsewhere on the board
/PCIE_X1_RX_P: C18.2; also elsewhere on the board
/PCIE_X1_TX_N: U2.127 (PE0_RX_N); also elsewhere on the board
/PCIE_X1_TX_P: U2.128 (PE0_RX_P); also elsewhere on the board
/SMB_CLK: U2.26 (SMBCLK); also elsewhere on the board
/SMB_DATA: U2.27 (SMBDATA); also elsewhere on the board
/nRST: U2.10 (nPERST); also elsewhere on the board
/pcie/CLK_O1_N: R21.2, R22.1; also elsewhere on the board
/pcie/CLK_O1_P: R20.2, R23.1; also elsewhere on the board
/pcie/CLK_O2_N: R19.2, R24.1; also elsewhere on the board
/pcie/CLK_O2_P: R18.2, R25.1; also elsewhere on the board
/pcie/RX_O1_N: U2.98 (PE1_RX_N); also elsewhere on the board
/pcie/RX_O1_P: U2.97 (PE1_RX_P); also elsewhere on the board
/pcie/RX_O2_N: U2.103 (PE2_RX_N); also elsewhere on the board
/pcie/RX_O2_P: U2.102 (PE2_RX_P); also elsewhere on the board
/pcie/TX_O1_N: C27.2; also elsewhere on the board
/pcie/TX_O1_P: C26.2; also elsewhere on the board
/pcie/TX_O2_N: C29.2; also elsewhere on the board
/pcie/TX_O2_P: C28.2; also elsewhere on the board
/pcie/mpcie1/nRST: U2.5 (nRST1); also elsewhere on the board
/pcie/mpcie2/nRST: U2.6 (nRST2); also elsewhere on the board
/pcie/switch/CLK0_N: R13.1, U2.83 (REFCLKO_0_N)
/pcie/switch/CLK0_P: R12.1, U2.85 (REFCLKO_0_P)
/pcie/switch/CLK1_N: R19.1, U2.80 (REFCLKO_1_N)
/pcie/switch/CLK1_P: R18.1, U2.81 (REFCLKO_1_P)
/pcie/switch/CLK2_N: R21.1, U2.77 (REFCLKO_2_N)
/pcie/switch/CLK2_P: R20.1, U2.78 (REFCLKO_2_P)
/pcie/switch/REFCLK_N: R13.2, R15.1, U2.111 (REFCLK_N)
/pcie/switch/REFCLK_P: R12.2, R17.1, U2.110 (REFCLK_P)
/pcie/switch/TX0_N: C19.1, U2.123 (PE0_TX_N)
/pcie/switch/TX0_P: C18.1, U2.124 (PE0_TX_P)
/pcie/switch/TX1_N: C27.1, U2.101 (PE1_TX_N)
/pcie/switch/TX1_P: C26.1, U2.100 (PE1_TX_P)
/pcie/switch/TX2_N: C29.1, U2.107 (PE2_TX_N)
/pcie/switch/TX2_P: C28.1, U2.106 (PE2_TX_P)
unnamed: J4.1, U2.67 (PORTSTATUS0)
unnamed: J4.2, U2.68 (PORTSTATUS1)
unnamed: J4.3, U2.69 (PORTSTATUS2)
unnamed: R26.1, U2.116 (REXT)
unnamed: R26.2, U2.115 (REXT_GND)
unnamed: R27.1, U2.86 (IREF)
unnamed: R28.1, U2.28 (PWR_SAV)
unnamed: R29.2, U2.42 (GPIO5)
unnamed: R30.2, U2.43 (GPIO6)
unnamed: R31.2, U2.44 (GPIO7)
unnamed: R32.2, U2.9 (TEST1)
unnamed: R33.2, U2.16 (TEST2)
unnamed: R34.2, U2.17 (TEST3)
unnamed: R35.2, U2.22 (TEST4)
unnamed: R36.2, U2.25 (TEST5)
unnamed: R37.2, U2.51 (TEST6)

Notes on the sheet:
Settings: CLKBUF_PD = 0, enable internal clock buffer & fanout VC1_EN = 0, disable virtual channel 1 RXPOLINV_DIS = 0, keep polarity inversion detection enabled PS_512B = 0, keep 256B packets SLOTCLK = 1, use global clock PWR_SAV = 0, disable power saving mode PRSNT[3:1] = 4, device present in slot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
Place close to end connector
Adjust clock series resistors between 10 and 30 ohms in case of overshoot / ringing
The PI7C9X2G404SL has an integrated clock buffer and fan-out, whose input is REFCLK_I. Yet it still needs a reference clock to work. Thus we feed it one of its clock output (REFCLKO_0) to its reference clock input (REFCLK).
For routing reasons, REFCLKO_1 and REFCLKO_2 are swapped

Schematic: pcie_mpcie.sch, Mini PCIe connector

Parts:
C30, C31: 100n; C_0402_1005Metric
D1: G; D_0603_1608Metric
D2: R; D_0603_1608Metric
D3: Y; D_0603_1608Metric
P3: MPCIE-Socket; mpcie-socket
R38, R39, R40: 270; R_0603_1608Metric

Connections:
/SMB_CLK: P3.30 (SMB_CLK); also elsewhere on the board
/SMB_DATA: P3.32 (SMB_DATA); also elsewhere on the board
/pcie/CLK_O1_N: P3.11 (RefClk-); also elsewhere on the board
/pcie/CLK_O1_P: P3.13 (RefClk+); also elsewhere on the board
/pcie/RX_O1_N: C30.1; also elsewhere on the board
/pcie/RX_O1_P: C31.1; also elsewhere on the board
/pcie/TX_O1_N: P3.33 (PETp0); also elsewhere on the board
/pcie/TX_O1_P: P3.31 (PETn0); also elsewhere on the board
/pcie/mpcie1/X1_R_N: C31.2, P3.23 (PERn0)
/pcie/mpcie1/X1_R_P: C30.2, P3.25 (PERp0)
/pcie/mpcie1/nRST: P3.22 (~PERST); also elsewhere on the board
unnamed: D1.1 (K), R38.1
unnamed: D2.1 (K), R39.1
unnamed: D3.1 (K), R40.1
unnamed: P3.42 (~LED_WWAN), R40.2
unnamed: P3.44 (~LED_WLAN), R39.2
unnamed: P3.46 (~LED_WPAN), R38.2

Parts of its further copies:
C32, C33: 100n; C_0402_1005Metric
D4: G; D_0603_1608Metric
D5: R; D_0603_1608Metric
D6: Y; D_0603_1608Metric
P4: MPCIE-Socket; mpcie-socket
R41, R42, R43: 270; R_0603_1608Metric

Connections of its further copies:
/SMB_CLK: P4.30 (SMB_CLK); also elsewhere on the board
/SMB_DATA: P4.32 (SMB_DATA); also elsewhere on the board
/pcie/CLK_O2_N: P4.11 (RefClk-); also elsewhere on the board
/pcie/CLK_O2_P: P4.13 (RefClk+); also elsewhere on the board
/pcie/RX_O2_N: C32.1; also elsewhere on the board
/pcie/RX_O2_P: C33.1; also elsewhere on the board
/pcie/TX_O2_N: P4.33 (PETp0); also elsewhere on the board
/pcie/TX_O2_P: P4.31 (PETn0); also elsewhere on the board
/pcie/mpcie2/X1_R_N: C33.2, P4.23 (PERn0)
/pcie/mpcie2/X1_R_P: C32.2, P4.25 (PERp0)
/pcie/mpcie2/nRST: P4.22 (~PERST); also elsewhere on the board
unnamed: D4.1 (K), R41.1
unnamed: D5.1 (K), R42.1
unnamed: D6.1 (K), R43.1
unnamed: P4.42 (~LED_WWAN), R43.2
unnamed: P4.44 (~LED_WLAN), R42.2
unnamed: P4.46 (~LED_WPAN), R41.2

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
